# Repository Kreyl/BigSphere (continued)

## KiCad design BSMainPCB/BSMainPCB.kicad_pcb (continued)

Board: 4 copper layers, 877 parts (153 on the bottom side), 377 nets, no tracks yet.

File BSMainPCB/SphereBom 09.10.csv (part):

Ref,Type,Quantity,Value,Footprint,Price,Sum,SP,SPDip,SP Total,PN,URL,Description,
"ANT1,",,1,ANT_PCB_MONO_2PIN,Radio:ANT_868_IFA_SIMPLEJOY,0,0,0,0,0,,,,do not mount
"BLN1,",,1,BALUN868JOHANSON,Radio:BALUN_JOHANSON868,59,59,2,0,2,0896BM15A0001E,https://www.terraelectronica.ru/product/602137,,
"C1,",Capacitor,1,10n,Capacitors:CAP_0603,"0,3","0,3",2,0,2,CL10B103KC8NNNC,https://www.terraelectronica.ru/product/863309,,"Any Capacitor 10n case 0603, x5r or x7r or np0 isolator"
"C2, C30,",,2,100u,Capacitors:SMD_D6d3,"2,66","5,32",2,0,4,CA016M0100RED-0605,https://onelec.ru/products/ca016m0100red-0605,https://spb.terraelectronica.ru/product/574304 3.4,
"C3,",Capacitor,1,2u2,Capacitors:CAP_0603,"0,58","0,58",2,0,2,CL10A225KQ8NNNC,https://www.terraelectronica.ru/product/863292,,"Any Capacitor 2u2 case 0603, x5r or x7r or np0 isolator"
"C6, C70, C41, C71, C42, C44, C73, C72, C43, C46, C76, C75, C74, C45, C47, C114, C144, C143, C116, C145, C142, C113, C118, C148, C147, C146, C115, C117, C119, C216, C214, C188, C186, C217, C215, C185, C191, C189, C218, C187, C220, C190, C219, C291, C262, C292, C259, C290, C261, C263, C257, C287, C289, C258, C260, C286, C288, C49, C79, C78, C51, C80, C77, C226, C197, C227, C194, C225, C196, C198, C48, C53, C83, C82, C81, C50, C52, C54, C192, C121, C150, C123, C151, C152, C149, C120, C125, C155, C154, C153, C124, C122, C126, C222, C224, C193, C195, C221, C223, C299, C298, C269, C266, C297, C268, C265, C264, C294, C270, C296, C267, C293, C295, C5, C29, C328, C344, C343, C329, C331, C346, C345, C330, C347, C349, C334, C332, C348, C333,",,129,10u,Capacitors:CAP_0805 25,"3,17","408,93",2,0,258,CC0805KKX5R6BB106,https://onelec.ru/products/cc0805kkx5r6bb106,https://spb.terraelectronica.ru/product/573665 4.0,
"C8, C15, C4, C11,",Capacitor,4,18pF,Capacitors:CAP_0603,"0,27","1,08",2,0,8,CC0603JRNPO9BN180,https://www.terraelectronica.ru/product/326939,,"Any Capacitor 18pF case 0603, x5r or x7r or np0 isolator"
"C23, C40, C69, C112, C141, C184, C213, C256, C285, C335,",,10,1000u,Capacitors:CAP_10xxR,"4,34","43,4",2,0,20,JRB1E102M05001000210000B,https://onelec.ru/products/jrb1e102m05001000210000b,,
"C25, C12, C18, C20, C16, C9, C21, C14, C40, C37, C39, C36, C34, C32, C99, C100, C102, C101, C104, C103, C105, C172, C174, C171, C176, C173, C177, C175, C246, C244, C245, C247, C249, C243, C248, C320, C315, C321, C319, C317, C316, C318, C107, C109, C255, C250, C256, C254, C252, C106, C111, C108, C112, C110, C181, C179, C178, C183, C182, C184, C180, C251, C253, C327, C326, C328, C322, C324, C325, C323, C28, C361, C359, C364, C360, C362, C363, C358, C10, C13, C17, C19, C22, C24, C26, C27,",Capacitor,23,0.1u,Capacitors:CAP_0603,"0,27","6,21",2,0,46,CL10B104KB8NNND,https://www.terraelectronica.ru/product/863315,,"Any Capacitor 0.1u case 0603, x5r or x7r or np0 isolator"
"C25, C12, C18, C20, C16, C9, C21, C14, C39, C37, C38, C36, C34, C32, C28, C10, C13, C19, C22, C24, C26, C27, C17,",Capacitor,65,1u,Capacitors:CAP_0603,"0,34","22,1",2,0,130,CL10A105KA8NNNC,https://www.terraelectronica.ru/product/882689,,"Any Capacitor 1u case 0603, x5r or x7r or np0 isolator"
"C33,",Capacitor,1,100pF,Capacitors:CAP_0402,"0,13","0,13",2,0,2,CC0402KRX7R9BB101,https://www.terraelectronica.ru/product/1910184,,"Any Capacitor 100pF case 0402, x5r or x7r or np0 isolator"
"C35,",Capacitor,1,2pF,Capacitors:CAP_0402,"0,22","0,22",2,0,2,CC0402BRNPO9BN2R2,https://www.terraelectronica.ru/product/1640553,,"Any Capacitor 2pF case 0402, x5r or x7r or np0 isolator"
"C38,",,1,DoNotMount,Capacitors:CAP_0402,0,0,0,0,0,-,-,,do not mount
"D1, D2,",PN,2,PMEG2020,Diodes:SOD323,"5,5",11,2,0,4,PMEG2020EJ.115,https://www.terraelectronica.ru/product/192057,,
"D3, D4, D5, D6, D7, D8, D10, D9, D11,",,9,LED,LEDs:LED_0805,"2,6","23,4",2,0,18,L-C170GCT,https://www.terraelectronica.ru/product/197403,красные,
"D12,",,1,LED,LEDs:LED_0603,,0,2,0,2,L-C191KGCT,https://www.terraelectronica.ru/product/1042561,Цвет?,
"DA1,",,1,ST1S10,SO_DIL_TSSOP:SO8HEATSINK,"52,89","52,89",8,0,8,ST1S10PUR,https://onelec.ru/products/st1s10pur,,
"DA2, DA3, DA5, DA4, DA7, DA6, DA8, DA17, DA19, DA16, DA21, DA18, DA22, DA20, DA33, DA31, DA34, DA32, DA36, DA35, DA30, DA44, DA49, DA50, DA46, DA48, DA45, DA47, DA10, DA12, DA37, DA42, DA43, DA39, DA41, DA9, DA14, DA11, DA15, DA13, DA24, DA26, DA23, DA28, DA25, DA27, DA29, DA38, DA40, DA56, DA51, DA57, DA53, DA55, DA52, DA54, DA59, DA61, DA64, DA60, DA62, DA58, DA63,",,63,ST1CC40_SO8,SO_DIL_TSSOP:SO8_150MIL,91,5733,8,0,504,ST1CC40DR,https://www.terraelectronica.ru/product/1198932,,
"DD1,",PN,1,CC1101,QFN_DFN:QFN20,207,207,20,0,20,СС1101RGPR,https://www.terraelectronica.ru/product/1185313,,
"DD2,",PN,1,STM32F405RX-64,LQFP_TQFP:LQFP64,459,459,64,0,64,STM32F405RGT6TR,https://www.terraelectronica.ru/product/1291543,,
"DD5, DD4, DD6, DD8, DD9, DD10, DD7, DD3,",,8,74HC595,SO_DIL_TSSOP:SO16_150MIL,"6,3","50,4",16,0,128,74HC595D,https://www.terraelectronica.ru/product/172998,,
"F1,",,1,Fuse0R,0,,0,0,0,0,-,-,,do not mount
"HOLE3, HOLE2, HOLE1, HOLE4, HOLE6, HOLE5, HOLE8, HOLE7, HOLE10, HOLE9, HOLE12, HOLE11,",,12,HOLE_METALLED,PCB:Hole3_5_out6mm,0,0,0,0,0,-,-,,do not mount
"L2,",,1,10u,Inductors:IND_SDR0604,67,67,2,0,2,SR0604100MLB,https://spb.terraelectronica.ru/product/1105487,,
"L3, L1,",PN,2,BLM15AG102,Inductors:IND_0402,"0,47","0,94",2,0,4,BLM15AG102SN1,https://spb.terraelectronica.ru/product/225140, 0,
"L4,",Inductor,1,1.2nH,Inductors:IND_0402,"4,7","4,7",2,0,2,LQP15MN1N2B02D,https://www.terraelectronica.ru/product/1995635,,Any Inductor 1.2nH case 0402
"L5, L6, L8, L7, L10, L11, L9, L20, L22, L21, L19, L24, L25, L23, L33, L35, L34, L36, L37, L38, L39, L53, L52, L51, L50, L48, L49, L47, L13, L15, L14, L12, L46, L45, L44, L17, L18, L16, L29, L27, L28, L26, L31, L32, L30, L43, L41, L42, L40, L60, L59, L58, L55, L56, L57, L54, L61, L63, L64, L62, L66, L65, L67,",,63,2.2uH,Inductors:IND_SRN2512,"7,27","458,01",2,0,126,SRN2512-2R2M,https://onelec.ru/products/srn2512-2r2m,https://spb.terraelectronica.ru/product/1638190 9.2,
"Logo1,",,1,Logo,Pictures:Ostranna_12d7_10d1,0,0,0,0,0,-,-,do not mount,
"Q1, Q3, Q5, Q7, Q9, Q11, Q13, Q15, Q17,",PN,9,2N7002,SOT:SOT23-3,"1,5","13,5",3,0,27,2N7002P.215,https://www.terraelectronica.ru/product/1068587,,
"Q2, Q4, Q6, Q8, Q10, Q12, Q14, Q16, Q18,",,9,IRF9321,SO_DIL_TSSOP:SO8HEATSINK,"21,06","189,54",8,0,72,IRF9321,https://onelec.ru/products/irf9321trpbf,https://spb.terraelectronica.ru/product/604773 26.7,
"R1,",Resistor,1,1M,Resistors:RES_0603,"0,12","0,12",2,0,2,RC0603FR-071ML,https://www.terraelectronica.ru/product/441621,,Any Resistor 1M case 0603 1%
"R3,",Resistor,1,2R0,Resistors:RES_0603,"0,16","0,16",2,0,2,RC0603FR-072RL,https://www.terraelectronica.ru/product/679314,,Any Resistor 2R0 case 0603 1%
"R13, R2,",Resistor,2,56k,Resistors:RES_0603,"0,12","0,24",2,0,4,RC0603FR-0756KL,https://www.terraelectronica.ru/product/542556,,Any Resistor 56k case 0603 1%
"R14, R20, R15, R4, R5, R7, R6, R9, R10, R11, R8, R12,",Resistor,12,1k,Resistors:RES_0603,"0,13","1,56",2,0,24,RC0603FR-071KL,https://www.terraelectronica.ru/product/542464,,Any Resistor 1k case 0603 1%
"R16,",Resistor,1,4k7,Resistors:RES_0603,"0,12","0,12",2,0,2,RC0603FR-074K7L,https://www.terraelectronica.ru/product/556296,,Any Resistor 4k7 case 0603 1%
"R17,",Resistor,1,1k5,Resistors:RES_0603,"0,12","0,12",2,0,2,RC0603FR-071K5L,https://www.terraelectronica.ru/product/327599,,Any Resistor 1k5 case 0603 1%
"R19, R22, R56, R72, R120, R122, R170, R186, R220,",Resistor,9,10k,Resistors:RES_0603,"0,14","1,26",2,0,18,CR-03FL7---10K,https://www.terraelectronica.ru/product/2781963,,Any Resistor 10k case 0603 1%
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
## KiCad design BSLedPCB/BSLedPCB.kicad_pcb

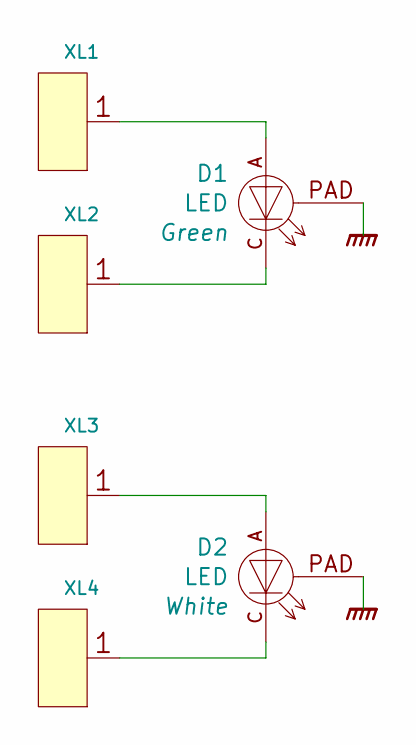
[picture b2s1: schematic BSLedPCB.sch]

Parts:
D1: LED; LED_XPE
D2: LED; Cree_XML
XL1, XL2, XL3, XL4: CONN_1; Oval3x1.5

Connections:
GNDPWR: D1.PAD, D2.PAD
unnamed: D1.A, XL1.1
unnamed: D1.C, XL2.1
unnamed: D2.A, XL3.1
unnamed: D2.C, XL4.1

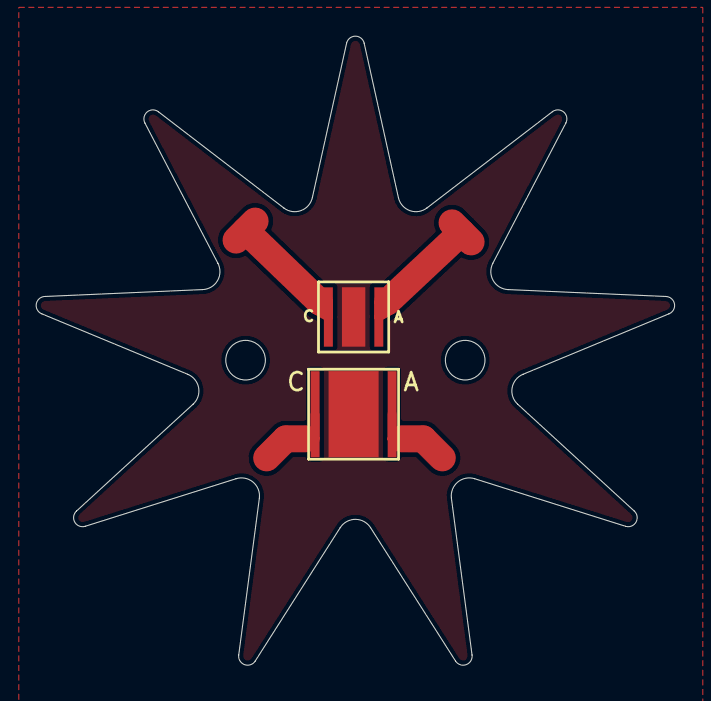
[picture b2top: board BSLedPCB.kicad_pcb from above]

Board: 2 copper layers, 35.5 x 34.9 mm, 6 parts (0 on the bottom side), 5 nets.

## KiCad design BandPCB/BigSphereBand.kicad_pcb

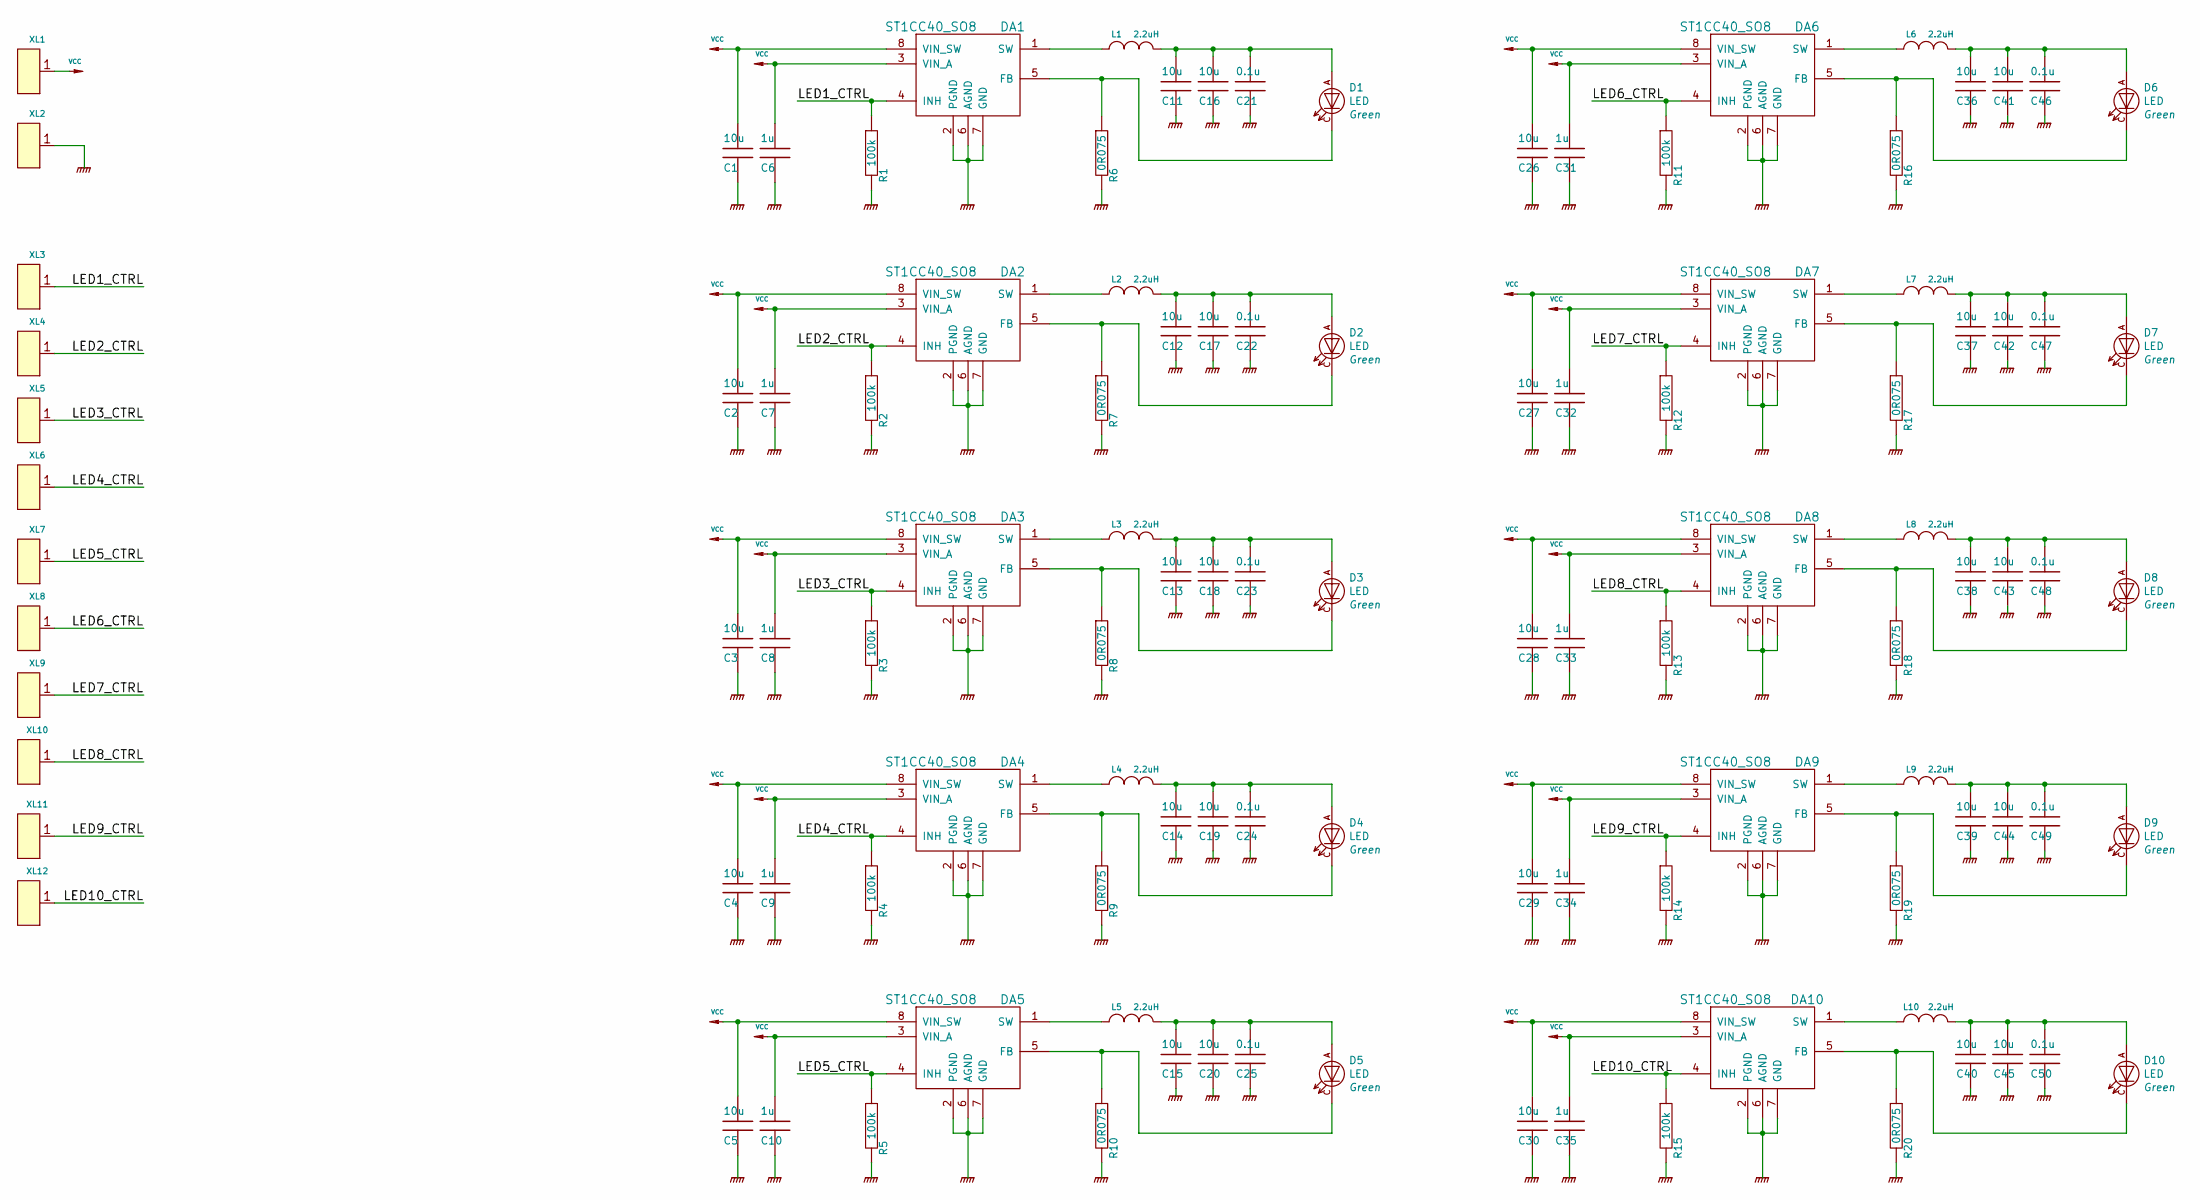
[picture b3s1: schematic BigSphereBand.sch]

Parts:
C1, C2, C3, C4, C5, C11, C12, C13, C14, C15, C16, C17, C18, C19, C20, C26, C27, C28, C29, C30, C36, C37, C38, C39, C40, C41, C42, C43, C44, C45: 10u; CAP_0603
C6, C7, C8, C9, C10, C31, C32, C33, C34, C35: 1u; CAP_0603
C21, C22, C23, C24, C25, C46, C47, C48, C49, C50: 0.1u; CAP_0603
D1, D2, D3, D4, D5, D6, D7, D8, D9, D10: LED; LED_XPE
DA1, DA2, DA3, DA4, DA5, DA6, DA7, DA8, DA9, DA10: ST1CC40_SO8; SO8_150MIL
L1, L2, L3, L4, L5, L6, L7, L8, L9, L10: 2.2uH; IND_SRN2512
R1, R2, R3, R4, R5, R11, R12, R13, R14, R15: 100k; RES_0603
R6, R7, R8, R9, R10, R16, R17, R18, R19, R20: 0R075; RES_1206
XL1, XL2, XL3, XL4, XL5, XL6, XL7, XL8, XL9, XL10, XL11, XL12: CONN_1; Oval3x1.5

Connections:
/LED1_CTRL: DA1.4 (INH), R1.1, XL3.1
/LED2_CTRL: DA2.4 (INH), R2.1, XL4.1
/LED3_CTRL: DA3.4 (INH), R3.1, XL5.1
/LED4_CTRL: DA4.4 (INH), R4.1, XL6.1
/LED5_CTRL: DA5.4 (INH), R5.1, XL7.1
/LED6_CTRL: DA6.4 (INH), R11.1, XL8.1
/LED7_CTRL: DA7.4 (INH), R12.1, XL9.1
/LED8_CTRL: DA8.4 (INH), R13.1, XL10.1
/LED9_CTRL: DA9.4 (INH), R14.1, XL11.1
/LED10_CTRL: DA10.4 (INH), R15.1, XL12.1
GNDPWR: C1.2, C2.2, C3.2, C4.2, C5.2, C6.2, C7.2, C8.2, C9.2, C10.2, C11.2, C12.2, C13.2, C14.2, C15.2, C16.2, C17.2, C18.2, C19.2, C20.2, C21.2, C22.2, C23.2, C24.2, C25.2, C26.2, C27.2, C28.2, C29.2, C30.2, C31.2, C32.2, C33.2, C34.2, C35.2, C36.2, C37.2, C38.2, C39.2, C40.2, C41.2, C42.2, C43.2, C44.2, C45.2, C46.2, C47.2, C48.2, C49.2, C50.2, DA1.2 (PGND), DA1.6 (AGND), DA1.7 (GND), DA2.2 (PGND), DA2.6 (AGND), DA2.7 (GND), DA3.2 (PGND), DA3.6 (AGND), DA3.7 (GND), DA4.2 (PGND), DA4.6 (AGND), DA4.7 (GND), DA5.2 (PGND), DA5.6 (AGND), DA5.7 (GND), DA6.2 (PGND), DA6.6 (AGND), DA6.7 (GND), DA7.2 (PGND), DA7.6 (AGND), DA7.7 (GND), DA8.2 (PGND), DA8.6 (AGND), DA8.7 (GND), DA9.2 (PGND), DA9.6 (AGND), DA9.7 (GND), DA10.2 (PGND), DA10.6 (AGND), DA10.7 (GND), R1.2, R2.2, R3.2, R4.2, R5.2, R6.2, R7.2, R8.2, R9.2, R10.2, R11.2, R12.2, R13.2, R14.2, R15.2, R16.2, R17.2, R18.2, R19.2, R20.2, XL2.1
unnamed: C11.1, C16.1, C21.1, D1.A, L1.1
unnamed: C12.1, C17.1, C22.1, D2.A, L2.1
unnamed: C13.1, C18.1, C23.1, D3.A, L3.1
unnamed: C14.1, C19.1, C24.1, D4.A, L4.1
unnamed: C15.1, C20.1, C25.1, D5.A, L5.1
unnamed: C37.1, C42.1, C47.1, D7.A, L7.1
unnamed: C38.1, C43.1, C48.1, D8.A, L8.1
unnamed: C39.1, C44.1, C49.1, D9.A, L9.1
unnamed: C40.1, C45.1, C50.1, D10.A, L10.1
unnamed: C36.1, C41.1, C46.1, D6.A, L6.1
unnamed: D1.C, DA1.5 (FB), R6.1
unnamed: D2.C, DA2.5 (FB), R7.1
unnamed: D3.C, DA3.5 (FB), R8.1
unnamed: D4.C, DA4.5 (FB), R9.1
unnamed: D5.C, DA5.5 (FB), R10.1
unnamed: D6.C, DA6.5 (FB), R16.1
unnamed: D7.C, DA7.5 (FB), R17.1
unnamed: D8.C, DA8.5 (FB), R18.1
unnamed: D9.C, DA9.5 (FB), R19.1
unnamed: D10.C, DA10.5 (FB), R20.1
unnamed: DA1.1 (SW), L1.2
unnamed: DA2.1 (SW), L2.2
unnamed: DA3.1 (SW), L3.2
unnamed: DA6.1 (SW), L6.2
unnamed: DA4.1 (SW), L4.2
unnamed: DA5.1 (SW), L5.2
unnamed: DA7.1 (SW), L7.2
unnamed: DA8.1 (SW), L8.2
unnamed: DA9.1 (SW), L9.2
unnamed: DA10.1 (SW), L10.2
VCC: C1.1, C2.1, C3.1, C4.1, C5.1, C6.1, C7.1, C8.1, C9.1, C10.1, C26.1, C27.1, C28.1, C29.1, C30.1, C31.1, C32.1, C33.1, C34.1, C35.1, DA1.3 (VIN_A), DA1.8 (VIN_SW), DA2.3 (VIN_A), DA2.8 (VIN_SW), DA3.3 (VIN_A), DA3.8 (VIN_SW), DA4.3 (VIN_A), DA4.8 (VIN_SW), DA5.3 (VIN_A), DA5.8 (VIN_SW), DA6.3 (VIN_A), DA6.8 (VIN_SW), DA7.3 (VIN_A), DA7.8 (VIN_SW), DA8.3 (VIN_A), DA8.8 (VIN_SW), DA9.3 (VIN_A), DA9.8 (VIN_SW), DA10.3 (VIN_A), DA10.8 (VIN_SW), XL1.1

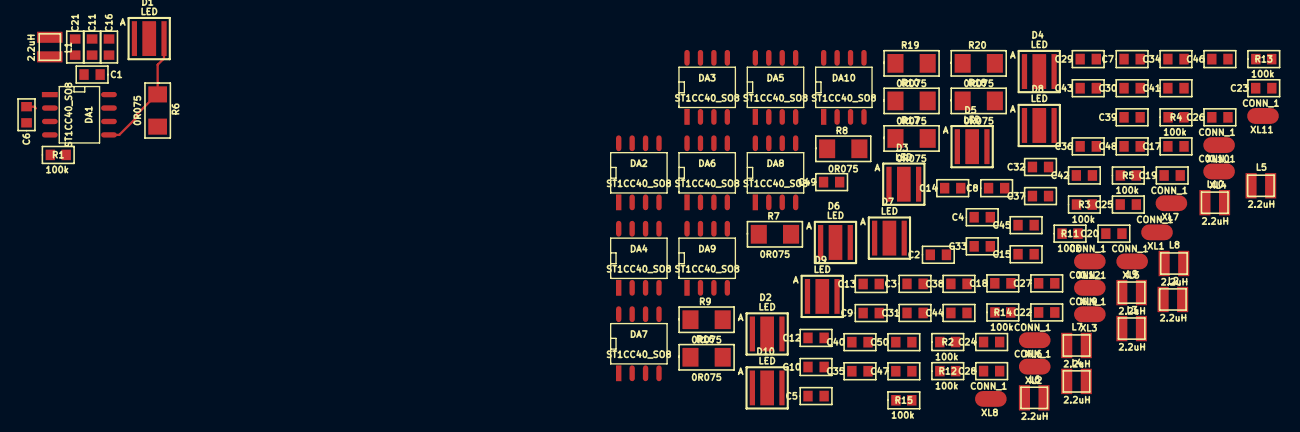
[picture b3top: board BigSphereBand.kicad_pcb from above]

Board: 2 copper layers, 112 parts (0 on the bottom side), 42 nets.

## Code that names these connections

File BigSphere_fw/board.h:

/*
 * board.h
 *
 *  Created on: 12 ñåíò. 2015 ã.
 *      Author: Kreyl
 */

#pragma once

// ==== General ====
#define BOARD_NAME          "BigSphere01"
#define APP_NAME            "BigSphere"

// MCU type as defined in the ST header.
#define STM32F205xx

// Freq of external crystal if any. Leave it here even if not used.
#define CRYSTAL_FREQ_HZ 12000000

// OS timer settings
#define STM32_ST_IRQ_PRIORITY   2
#define STM32_ST_USE_TIMER      5
#define SYS_TIM_CLK             (Clk.GetTimInputFreq(TIM5))

//  Periphery
#define I2C1_ENABLED            FALSE
#define I2C2_ENABLED            FALSE
#define I2C3_ENABLED            FALSE
#define SIMPLESENSORS_ENABLED   FALSE
#define BUTTONS_ENABLED         FALSE

#define ADC_REQUIRED            FALSE

#if 1 // ========================== GPIO =======================================
// EXTI
#define INDIVIDUAL_EXTI_IRQ_REQUIRED    FALSE

// Debug pin
#define DBG_PIN         GPIOB, 5
#define DBG_HI()        PinSetHi(DBG_PIN)
#define DBG_LO()        PinSetLo(DBG_PIN)
#define DBG_TOGGLE()    PinToggle(DBG_PIN)

// UART
#define UART_GPIO       GPIOB
#define UART_TX_PIN     6
#define UART_RX_PIN     7

// Indication
#define BLINK_LED       GPIOB, 8, omPushPull
#define LED_PWR1        GPIOA, 8, omPushPull
#define LED_PWR2        GPIOA, 10, omPushPull
#define LED_PWR3        GPIOA, 15, omPushPull
#define LED_PWR4        GPIOB, 9, omPushPull
#define LED_PWR5        GPIOB, 10, omPushPull
#define LED_PWR6        GPIOB, 11, omPushPull
#define LED_PWR7        GPIOD, 2, omPushPull
#define LED_PWR8        GPIOC, 14, omPushPull
#define LED_PWR9        GPIOC, 15, omPushPull

// LED registers
#define LED_MOSI        GPIOB, 15, omPushPull, pudNone, AF5
#define LED_CLK         GPIOB, 13, omPushPull, pudNone, AF5
#define LED_LATCH       GPIOB, 12
#define LED_OE          GPIOB, 14

// LEDs
#define LEDS_CNT        63
#define LEDS_BYTE_CNT   8 // 63 bits => 8 bytes

// Power control
#define PWR_CNT         9
#define PWR_CTRL1       GPIOC, 4, omPushPull
#define PWR_CTRL2       GPIOC, 5, omPushPull
#define PWR_CTRL3       GPIOC, 6, omPushPull
#define PWR_CTRL4       GPIOC, 7, omPushPull
#define PWR_CTRL5       GPIOC, 9, omPushPull
#define PWR_CTRL6       GPIOC, 10, omPushPull
#define PWR_CTRL7       GPIOC, 11, omPushPull
#define PWR_CTRL8       GPIOC, 12, omPushPull
#define PWR_CTRL9       GPIOC, 13, omPushPull

#define VENT_CTRL       GPIOC, 8

// Buttons
#define BTN_PIN         GPIOB, 2, pudPullUp

// USB
#define USB_DETECT_PIN  GPIOA, 9
#define USB_DM          GPIOA, 11
#define USB_DP          GPIOA, 12
#define USB_AF          AF10

// Measurement
#define VOLT1           GPIOA, 1
#define VOLT2           GPIOA, 2
#define VOLT3           GPIOA, 3
#define VOLT4           GPIOC, 0
#define VOLT5           GPIOC, 1
#define VOLT6           GPIOC, 2
#define VOLT7           GPIOC, 3
#define VOLT8           GPIOB, 0
#define VOLT9           GPIOB, 1

// Radio: SPI, Sck,Miso,Mosi, Cs, GDO0
#define CC_Setup        SPI1, GPIOA, 5,6,7, GPIOA,4, GPIOA,0

#endif // GPIO

#if 1 // =========================== SPI =======================================
#define LEDS_SPI        SPI2
#endif

#if 1 // =========================== Timers ====================================
#define LEDS_TIM        TIM3
#define LEDS_TIM_IRQ_VECTOR VectorB4

#endif

#if I2C2_ENABLED // ====================== I2C ================================
#define I2C2_BAUDRATE   400000
#define I2C_PILL        i2c2
#endif

#if ADC_REQUIRED // ======================= Inner ADC ==========================
// Measuremen timing src
#define ADC_TIM             TIM2

// ADC channels
#define ADC_VOLTAGE_CH      4
#define ADC_CURRENT_CH      6
#define ADC_VREFINT_CH      17 // Constant

#define ADC_CHANNELS        { ADC_VOLTAGE_CH, ADC_CURRENT_CH, ADC_VREFINT_CH }
// Index in array
#define ADC_VOLTAGE_INDX    0
#define ADC_CURRENT_INDX    1
#define ADC_VREFINT_INDX    2

#define ADC_CHANNEL_CNT     3   // Do not use countof(AdcChannels) as preprocessor does not know what is countof => cannot check
#endif

#if 1 // =========================== DMA =======================================
#define STM32_DMA_REQUIRED  TRUE
// ==== Uart ====
// Remap is made automatically if required
#define UART_DMA_TX     STM32_DMA_STREAM_ID(2, 7)
#define UART_DMA_RX     STM32_DMA_STREAM_ID(2, 5)
#define UART_DMA_CHNL   4
#define UART_DMA_TX_MODE(Chnl) (STM32_DMA_CR_CHSEL(Chnl) | DMA_PRIORITY_LOW | STM32_DMA_CR_MSIZE_BYTE | STM32_DMA_CR_PSIZE_BYTE | STM32_DMA_CR_MINC | STM32_DMA_CR_DIR_M2P | STM32_DMA_CR_TCIE)
#define UART_DMA_RX_MODE(Chnl) (STM32_DMA_CR_CHSEL(Chnl) | DMA_PRIORITY_MEDIUM | STM32_DMA_CR_MSIZE_BYTE | STM32_DMA_CR_PSIZE_BYTE | STM32_DMA_CR_MINC | STM32_DMA_CR_DIR_P2M | STM32_DMA_CR_CIRC)

// ==== SPI ====
#define LEDS_SPI_DMA_TX STM32_DMA_STREAM_ID(1, 4)
#define LEDS_DMA_TX_CHNL   0
#define LEDS_DMA_TX_MODE  \
        (STM32_DMA_CR_CHSEL(LEDS_DMA_TX_CHNL) | \
        DMA_PRIORITY_LOW |     \
        STM32_DMA_CR_MSIZE_BYTE | \
        STM32_DMA_CR_PSIZE_BYTE | \
        /*STM32_DMA_CR_TCIE |*/ \
        STM32_DMA_CR_MINC |    /* Mem pointer increase */  \
        STM32_DMA_CR_DIR_M2P   /* Mem to peripheral */ )

#if I2C1_ENABLED // ==== I2C1 ====
#define I2C1_DMA_TX     STM32_DMA1_STREAM6
#define I2C1_DMA_RX     STM32_DMA1_STREAM5
#endif
#if I2C2_ENABLED // ==== I2C2 ====
#define I2C2_DMA_TX     STM32_DMA1_STREAM7
#define I2C2_DMA_RX     STM32_DMA1_STREAM3
#endif

#if ADC_REQUIRED
#define ADC_DMA         STM32_DMA_STREAM_ID(2, 0)
#define ADC_DMA_MODE    STM32_DMA_CR_CHSEL(0) |   /* DMA2 Stream0 Channel0 */ \
                        DMA_PRIORITY_LOW | \
                        STM32_DMA_CR_MSIZE_HWORD | \
                        STM32_DMA_CR_PSIZE_HWORD | \
                        STM32_DMA_CR_MINC |       /* Memory pointer increase */ \
                        STM32_DMA_CR_DIR_P2M |    /* Direction is peripheral to memory */ \
                        STM32_DMA_CR_CIRC |       /* Circulate */ \
                        STM32_DMA_CR_TCIE         /* Enable Transmission Complete IRQ */
#endif // ADC

#endif // DMA

#if 1 // ========================== USART ======================================
#define PRINTF_FLOAT_EN FALSE
#define UART_TXBUF_SZ   256
#define UART_RXBUF_SZ   99

#define UARTS_CNT       1

#define CMD_UART_PARAMS \
    USART1, UART_GPIO, UART_TX_PIN, UART_GPIO, UART_RX_PIN, \
    UART_DMA_TX, UART_DMA_RX, UART_DMA_TX_MODE(UART_DMA_CHNL), UART_DMA_RX_MODE(UART_DMA_CHNL)

#endif

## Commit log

2019-10-01 PCB started
2019-10-01 Proceeding
2019-10-05 Main PCB sch seems done
2019-10-05 Layout started
2019-10-06 - Lot of capacitors near LEDs removed, as eDesignSuite shows they are not required
2019-10-07 * Hole connection changed
2019-10-08 Proceeding with layout
2019-10-08 Layout done
2019-10-09 BOMS added
2019-10-11 + Tracing done
2019-10-11 + gitignore
2019-10-11 PCB sent to factory
2019-10-24 + working on fw started
2019-10-24 board.h seems prepared
2019-10-25 + Leds seem to show pic
2019-10-25 minor
2019-10-26 + Radio works
2019-10-26 + Antenna matched
2019-10-29 + Effects work * Freq now 120MHz
2019-10-29 + Button
2019-10-31 + Switch to other effect when button pressed * Fixed bug with 0xFF=Forever (now rellay equals) - UART RX with threads etc. - RTOS minimized. One thread left only.
2019-11-01 + Release hex
2019-12-02 Release
